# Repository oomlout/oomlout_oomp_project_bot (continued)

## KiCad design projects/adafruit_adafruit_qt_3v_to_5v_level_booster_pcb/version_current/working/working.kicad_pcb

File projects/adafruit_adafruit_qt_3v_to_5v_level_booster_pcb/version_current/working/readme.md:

# OOMP Project  
## Adafruit-QT-3V-to-5V-Level-Booster-PCB  by adafruit  
  
oomp key: oomp_projects_flat_adafruit_adafruit_qt_3v_to_5v_level_booster_pcb  
(snippet of original readme)  
  
-- Adafruit QT 3V to 5V Level Booster Breakout - STEMMA QT / Qwiic PCB  
  
<a href="http://www.adafruit.com/products/5649"><br/>  
Click here to purchase one from the Adafruit shop</a>  
  
PCB files for the Adafruit QT 3V to 5V Level Booster Breakout - STEMMA QT.   
  
Format is EagleCAD schematic and board layout  
* https://www.adafruit.com/product/5649  
  
--- Description  
  
If you're looking to use the Qwiic / Stemma QT standard for your next project - but you're using a sensor or device that requires 5V power or logic, this board is designed for you! It will let you use the 3V power and logic from your Raspberry Pi, or ARM Cortex microcontroller, and boost/shift it up to 5V for use with older or high-power devices that aren't happy with only 3V.  
  
These days, almost every microcontroller / microcomputer board has 3V power and logic: ESP32 series, ATSAMD chips, RP2040 boards, micro:bits, etc! But we still see sensors and devices here and there that really want 5V power or logic. Like this Sensirion SEN54 which has a small motor with 5V power requirements.  
  
On one side of this board is 3V power and logic level inputs. In the middle is a 5V charge-pump boosting regulator that can provide 100mA continuous (250mA peak) plus level shifting circuitry. On the opposite side is the same I2C traffic but now safely shifted up to 5V. If you happen to be using a board that wants 5V power, but 3V logic I2C, there's a solder jumper on the back you can cut/s  
  full source readme at [readme_src.md](readme_src.md)  
  
source repo at: [https://github.com/adafruit/Adafruit-QT-3V-to-5V-Level-Booster-PCB](https://github.com/adafruit/Adafruit-QT-3V-to-5V-Level-Booster-PCB)  
## Board  

## Schematic  

[schematic pdf](working_schematic.pdf)  
## Images

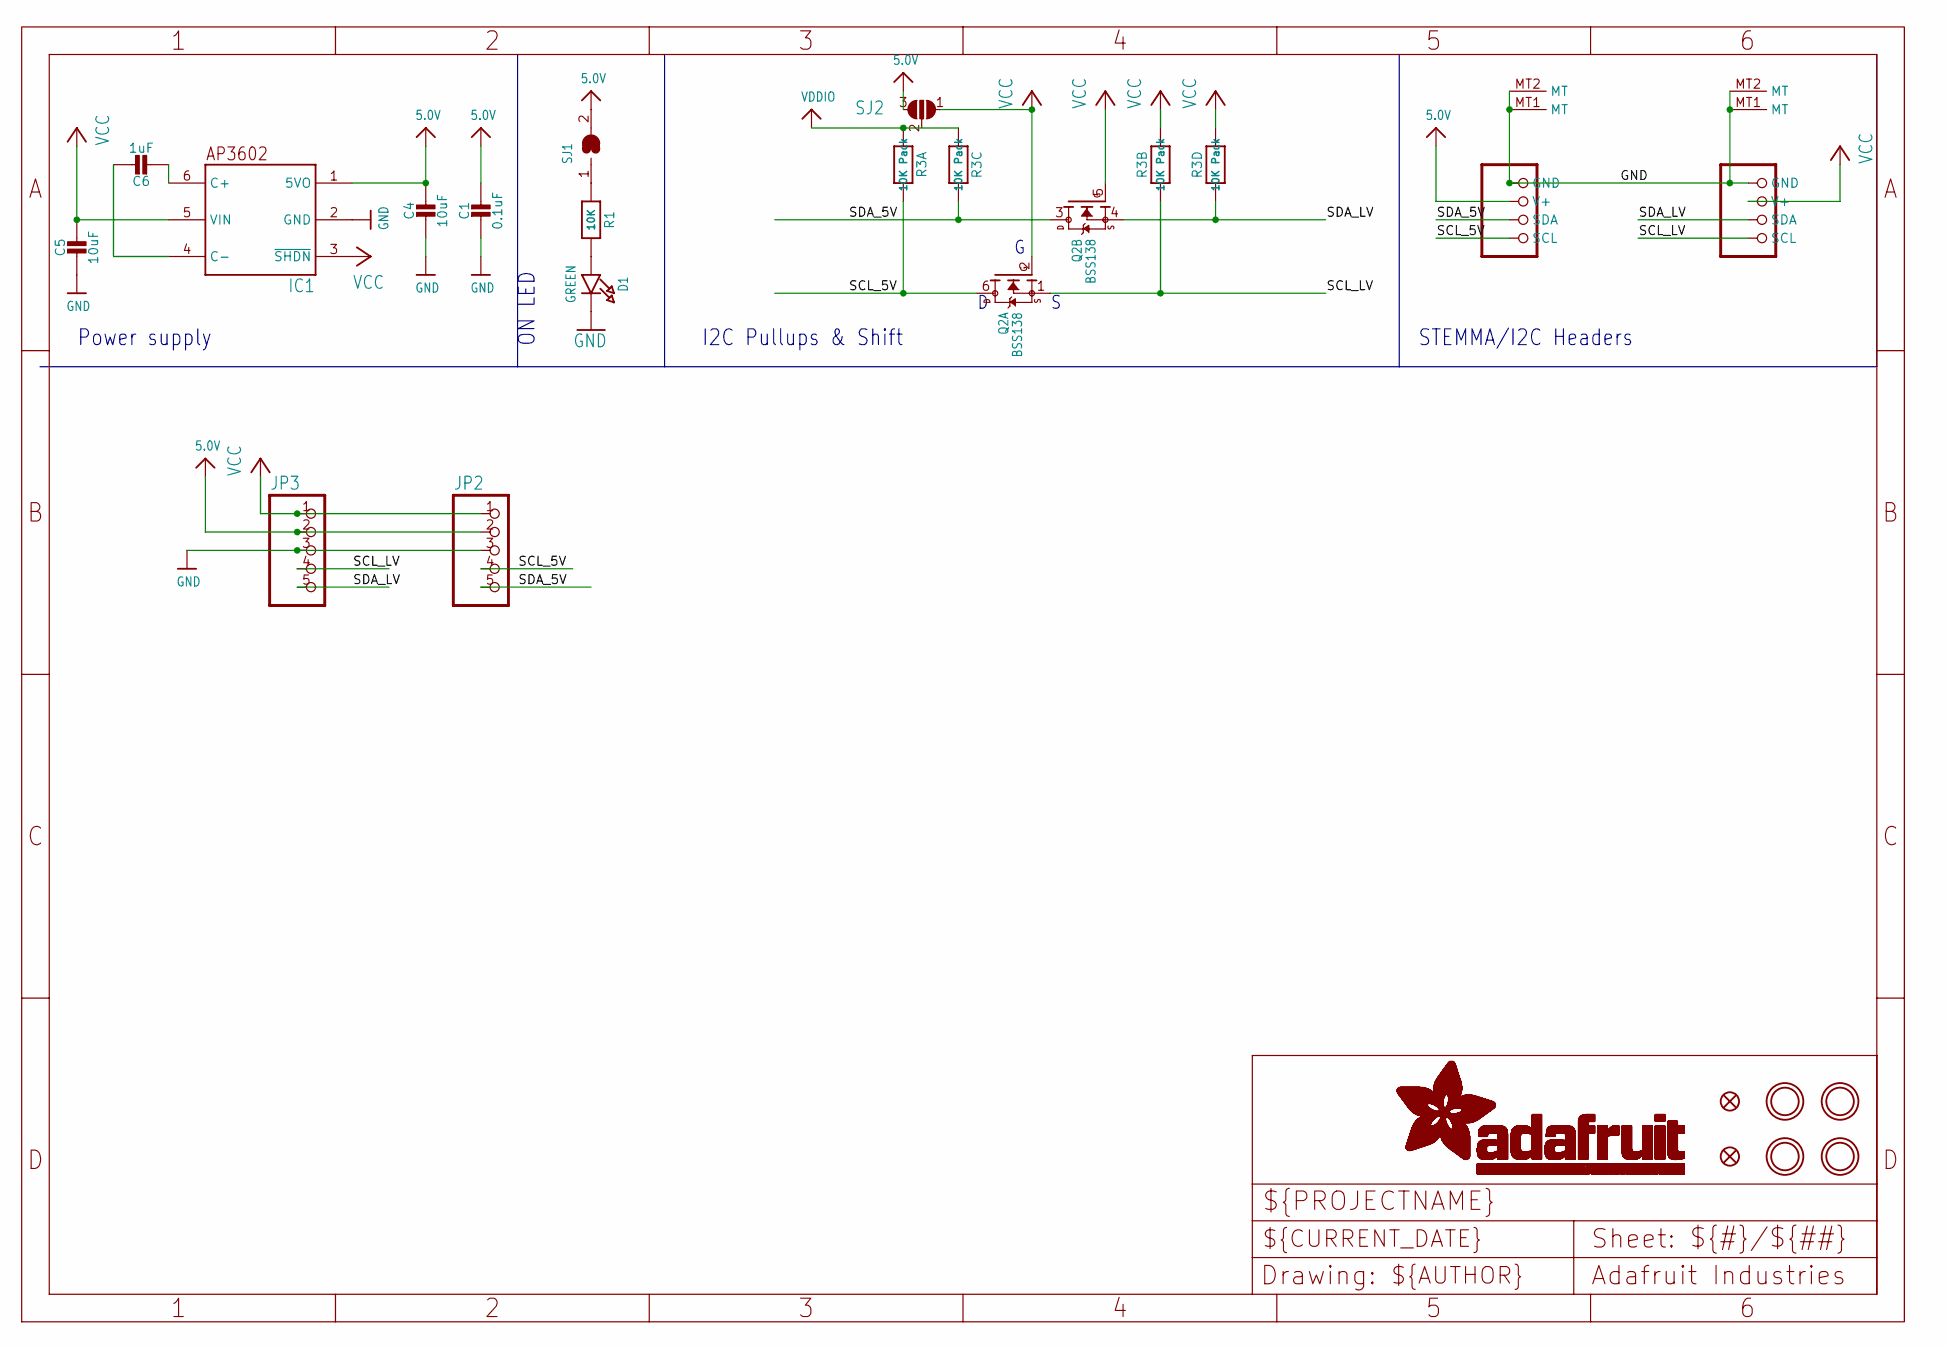
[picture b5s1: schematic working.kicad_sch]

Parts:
C1: 0.1uF; 0603-NO
C4, C5: 10uF; 0805-NO
C6: 1uF; 0805-NO
CONN3, CONN4: STEMMA_I2C_QT; JST_SH4
D1: GREEN; CHIPLED_0603_NOOUTLINE
FID3, FID4: FIDUCIAL_1MM
IC1: AP3602; SOT23-6
JP2, JP3: HEADER-1X576MIL; 1X05_ROUND_76
Q2: BSS138; SOT363
R1: 10K; 0603-NO
R3: 10K Pack; RESPACK_4X0603
SJ1: SOLDERJUMPERCLOSED; SOLDERJUMPER_CLOSEDWIRE
SJ2: SOLDERJUMPER_2WAY; SOLDERJUMPER_2WAY_OPEN_NOPASTE
U$1, U$17, U$19, U$21: MOUNTINGHOLE2.5; MOUNTINGHOLE_2.5_PLATED

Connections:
5.0V: C1.1, C4.1, CONN3.2 (V+), IC1.1 (5VO), JP2.2, JP3.2, SJ1.2, SJ2.3
GND: C1.2, C4.2, C5.2, CONN3.1 (GND), CONN3.MT1 (MT), CONN3.MT2 (MT), CONN4.1 (GND), CONN4.MT1 (MT), CONN4.MT2 (MT), D1.C, IC1.2 (GND), JP2.3, JP3.3
unnamed: D1.A, R1.2
unnamed: R1.1, SJ1.1
unnamed: C6.2, IC1.6 (C+)
unnamed: C6.1, IC1.4 (C-)
SCL_5V: CONN3.4 (SCL), JP2.4, Q2.6 (D), R3.8 (2)
SCL_LV: CONN4.4 (SCL), JP3.4, Q2.1 (S), R3.7 (2)
SDA_5V: CONN3.3 (SDA), JP2.5, Q2.3 (D), R3.6 (2)
SDA_LV: CONN4.3 (SDA), JP3.5, Q2.4 (S), R3.5 (2)
VCC: C5.1, CONN4.2 (V+), IC1.3 (~SHDN), IC1.5 (VIN), JP2.1, JP3.1, Q2.2 (G), Q2.5 (G), R3.2 (1), R3.4 (1), SJ2.1
VDDIO: R3.1, R3.3 (1), SJ2.2

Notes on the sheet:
ON LED
Power supply
STEMMA/I2C Headers
I2C Pullups & Shift

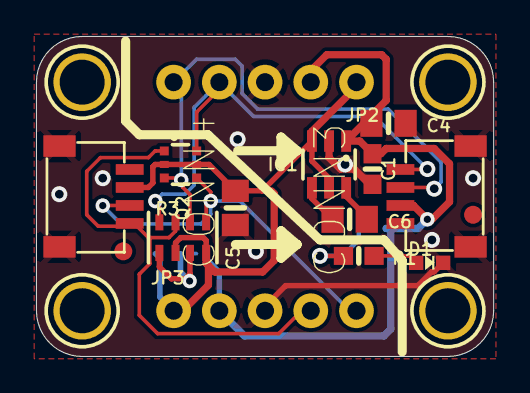
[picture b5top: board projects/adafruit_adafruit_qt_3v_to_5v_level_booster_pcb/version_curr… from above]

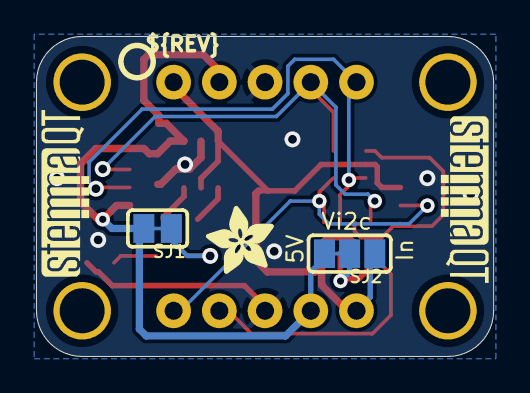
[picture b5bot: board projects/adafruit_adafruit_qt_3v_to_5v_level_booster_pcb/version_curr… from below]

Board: 2 copper layers, 25.4 x 17.8 mm, 40 parts (8 on the bottom side), 12 nets.

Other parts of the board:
PLABEL0: PLABEL0
PLABEL1: PLABEL1
PLABEL2: PLABEL2
PLABEL3: PLABEL3
PLABEL4: PLABEL4
PLABEL5: PLABEL5
PLABEL6: PLABEL6
PLABEL7: PLABEL7
PLABEL8: PLABEL8
PLABEL9: PLABEL9
PLABEL10: PLABEL10
PLABEL11: PLABEL11
PLABEL12: PLABEL12
PLABEL13: PLABEL13
PLABEL14: PLABEL14
U$2: ADAFRUIT_3.5MM
U$25: PCBFEAT-REV-040
U$30, U$31: STEMMAQT

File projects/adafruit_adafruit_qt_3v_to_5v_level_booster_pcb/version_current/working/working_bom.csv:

Row,Description,Part,References,Value,Footprint,Quantity Per PCB,Status,Datasheet
1,,CAP_CERAMIC0603_NO,C1,0.1uF,0603-NO,1, ,
2,,CAP_CERAMIC0805-NOOUTLINE,C6,1uF,0805-NO,1, ,
3,,CAP_CERAMIC0805-NOOUTLINE,C4 C5,10uF,0805-NO,2, ,
4,,STEMMA_I2C_QT,CONN3 CONN4,STEMMA_I2C_QT,JST_SH4,2, ,
5,,LED0603_NOOUTLINE,D1,GREEN,CHIPLED_0603_NOOUTLINE,1, ,
6,,AP3602,IC1,AP3602,SOT23-6,1, ,
7,,HEADER-1X576MIL,JP2 JP3,HEADER-1X576MIL,1X05_ROUND_76,2, ,
8,,MOSFET-N_DUAL,Q2,BSS138,SOT363,1, ,
9,,RESISTOR_0603_NOOUT,R1,10K,0603-NO,1, ,
10,,RESISTOR_4PACK,R3,10K Pack,RESPACK_4X0603,1, ,





Project info:
Schematic:,working
Variant:,default
Revision:,
Date:,2023-08-03_17-21-23
KiCad Version:,7.0.6-7.0.6~ubuntu22.04.1
Statistics:
Component Groups:,10
Component Count:,13 (0 SMD/ 0 THT)
Fitted Components:,13 (0 SMD/ 0 THT)
Number of PCBs:,1
Total Components:,13

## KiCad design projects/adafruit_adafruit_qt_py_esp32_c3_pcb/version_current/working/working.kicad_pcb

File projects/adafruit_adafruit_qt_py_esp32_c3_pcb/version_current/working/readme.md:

# OOMP Project  
## Adafruit-QT-Py-ESP32-C3-PCB  by adafruit  
  
oomp key: oomp_projects_flat_adafruit_adafruit_qt_py_esp32_c3_pcb  
(snippet of original readme)  
  
-- Adafruit QT Py ESP32-C3 WiFi Dev Board with STEMMA QT PCB  
  
<a href="http://www.adafruit.com/products/5405"><br/>  
Click here to purchase one from the Adafruit shop</a>  
  
PCB files for the Adafruit QT Py ESP32-C3 WiFi Dev Board with STEMMA QT.   
  
Format is EagleCAD schematic and board layout  
* https://www.adafruit.com/product/5405  
  
--- Description  
  
What's life without a little RISC? This miniature dev board is perfect for small projects: it comes with our favorite connector - the STEMMA QT, a chainable I2C port, WiFi, Bluetooth LE, and plenty of FLASH and RAM memory for many IoT projects. What a cutie pie! Or is it... a QT Py? This diminutive dev board comes with a RISC-V IoT microcontroller, the ESP32-C3!  
  
ESP32-C3 is a low-cost microcontroller from Espressif that supports 2.4 GHz Wi-Fi and Bluetooth® Low Energy (Bluetooth LE). It has built-in USB-to-Serial, but not native USB - it cannot act as a keyboard or disk drive. The chip used here has 4MB of Flash memory, 400 KB of SRAM and can easily handle TLS connections.  
  
The ESP32-C3 integrates a rich set of peripherals, ranging from UART, I2C, I2S, remote control peripheral, LED PWM controller, general DMA controller, TWAI controller, USB Serial/JTAG controller, temperature sensor, and ADC. It also includes SPI, Dual SPI, and Quad SPI interfaces. There is no DAC or native capacitive touch.  
  
There's a minimum number of pins on this chip, it's specifically designed to be low cost   
  full source readme at [readme_src.md](readme_src.md)  
  
source repo at: [https://github.com/adafruit/Adafruit-QT-Py-ESP32-C3-PCB](https://github.com/adafruit/Adafruit-QT-Py-ESP32-C3-PCB)  
## Board  

## Schematic  

[schematic pdf](working_schematic.pdf)  
## Images

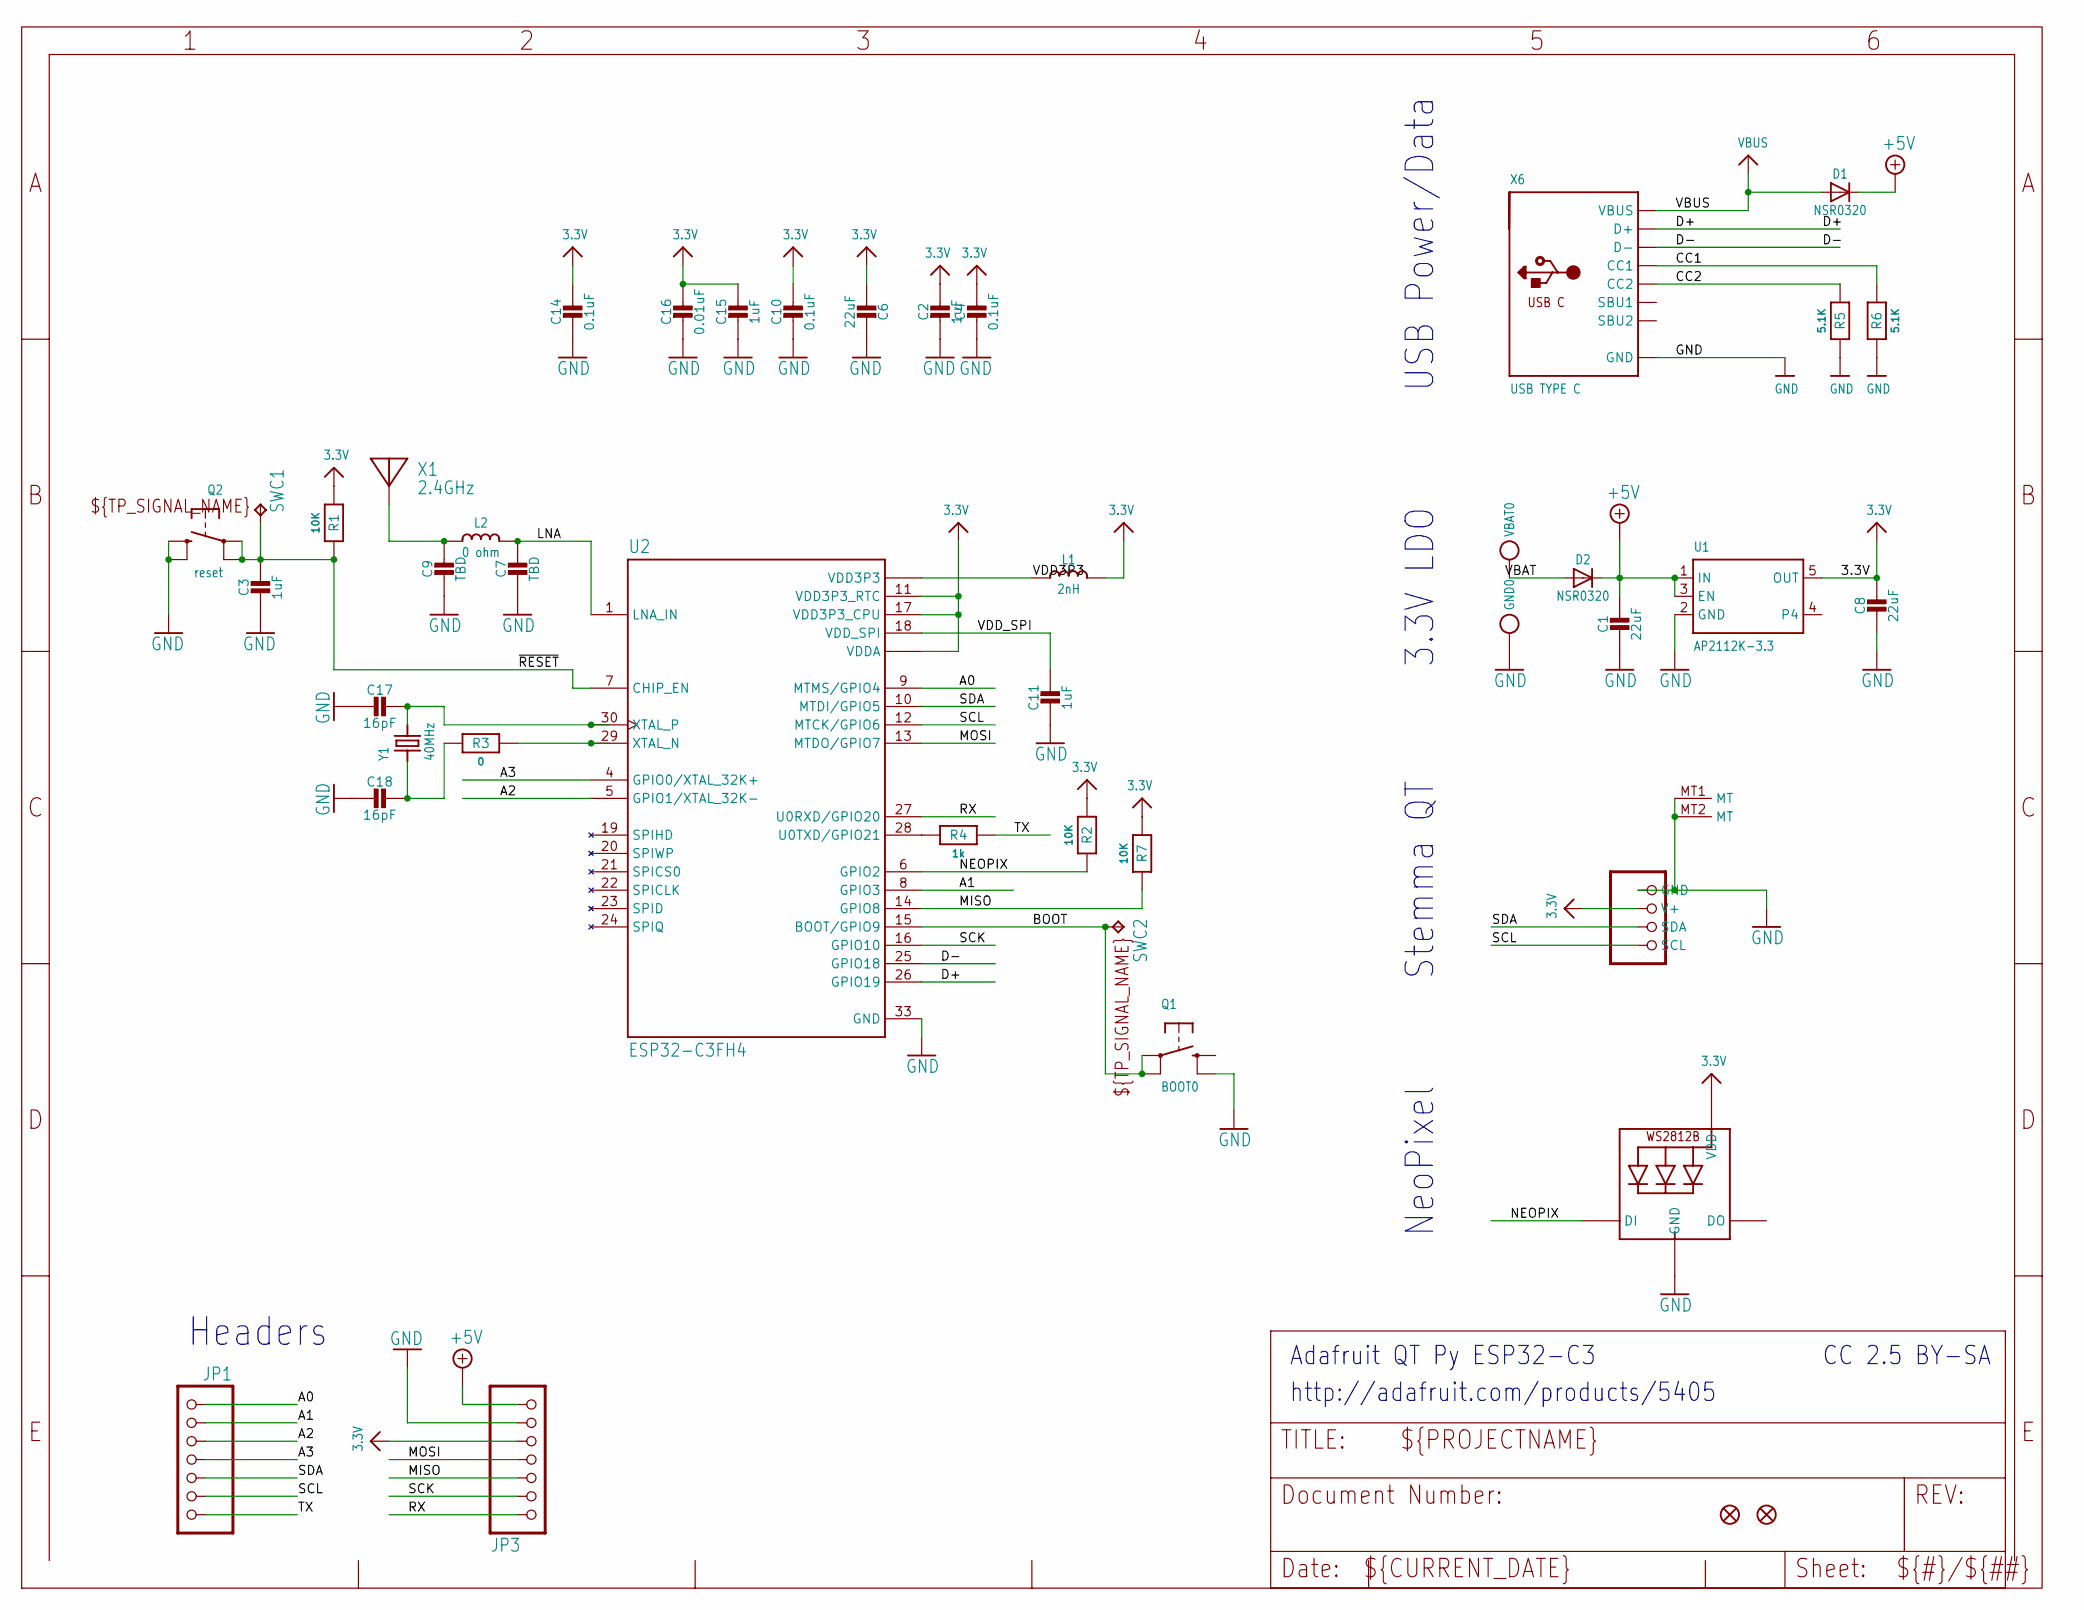
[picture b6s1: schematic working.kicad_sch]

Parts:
C1, C6, C8: 22uF; 0805-NO
C2, C3, C11, C15: 1uF; _0402NO
C4, C10, C14: 0.1uF; _0402NO
C7, C9: TBD; _0402NO
C16: 0.01uF; _0402NO
C17, C18: 16pF; _0402NO
CONN1: STEMMA_I2C_QTSKINNY; JST_SH4_SKINNY
D1, D2: NSR0320; SOD-323_MINI
GND0: TESTPOINT_MINUS; TESTPOINT_MINUS_1X3MM
JP1, JP3: HEADER-1X7_CASTEL; 1X07_CASTEL
L1: 2nH; _0402
L2: 0 ohm; _0402
LED1: WS2812B_SK6805_1515; SK6805_1515
Q1: BOOT0; BTN_KMR2_4.6X2.8
Q2: reset; BTN_KMR2_SLIM
R1, R2: 10K; _0402NO
R3: 0; _0402NO
R4: 1k; _0402NO
R5, R6: 5.1K; _0402NO
R7: 10K; _0603MP_TWO6MIL
SWC1, SWC2: TPB1,27; B1,27
U1: AP2112K-3.3; SOT23-5
U2: ESP32-C3FH4; QFN32_5MM
U$6, U$8: FIDUCIAL_1MM
VBAT0: TESTPOINT_PLUS13; TESTPOINT_PLUS_1X3MM
X1: 2.4GHz; ANT_2450AT18B100
X6: USB TYPE C; USB_C_CUSB31-CFM2AX-01-X
Y1: 40MHz; CRYSTAL_2X1.6

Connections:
3.3V: C2.1, C4.1, C6.1, C8.1, C10.1, C14.1, C15.1, C16.1, CONN1.2 (V+), JP3.5, JP3.5C (5), L1.1, LED1.2 (VDD), R1.1, R2.1, R7.1, U1.5 (OUT), U2.11 (VDD3P3_RTC), U2.17 (VDD3P3_CPU), U2.31 (VDDA), U2.32 (VDDA)
+5V: C1.1, D1.C, D2.C, JP3.7, JP3.7C (7), U1.1 (IN), U1.3 (EN)
A0: JP1.1, JP1.1C (1), U2.9 (MTMS/GPIO4)
A1: JP1.2, JP1.2C (2), U2.8 (GPIO3)
A2: JP1.3, JP1.3C (3), U2.5 (GPIO1/XTAL_32K-)
A3: JP1.4, JP1.4C (4), U2.4 (GPIO0/XTAL_32K+)
BOOT: Q1.A, Q1.A' (P1), SWC2.TP, U2.15 (BOOT/GPIO9)
CC1: R6.2, X6.A5 (CC1)
CC2: R5.2, X6.B5 (CC2)
D+: U2.26 (GPIO19), X6.A6 (D+), X6.B6 (D+)
D-: U2.25 (GPIO18), X6.A7 (D-), X6.B7 (D-)
GND: C1.2, C2.2, C3.2, C4.2, C6.2, C7.2, C8.2, C9.2, C10.2, C11.2, C14.2, C15.2, C16.2, C17.2, C18.2, CONN1.1 (GND), CONN1.MT1 (MT), CONN1.MT2 (MT), GND0.P$1, JP3.6, JP3.6C (6), LED1.4 (GND), Q1.B' (S1), Q2.B (S), Q2.B' (S1), R5.1, R6.1, U1.2 (GND), U2.33 (GND), X6.A1B12 (GND), X6.B1A12 (GND)
LNA: C7.1, L2.2, U2.1 (LNA_IN)
MISO: JP3.3, JP3.3C (3), R7.2, U2.14 (GPIO8)
MOSI: JP3.4, JP3.4C (4), U2.13 (MTDO/GPIO7)
unnamed: R4.1, U2.28 (U0TXD/GPIO21)
unnamed: C9.1, L2.1, X1.FP
unnamed: R3.2, U2.29 (XTAL_N)
unnamed: C17.1, U2.30 (XTAL_P), Y1.3 (2)
unnamed: C18.1, R3.1, Y1.1
NEOPIX: LED1.1 (DI), R2.2, U2.6 (GPIO2)
RX: JP3.1, JP3.1C (1), U2.27 (U0RXD/GPIO20)
SCK: JP3.2, JP3.2C (2), U2.16 (GPIO10)
SCL: CONN1.4 (SCL), JP1.6, JP1.6C (6), U2.12 (MTCK/GPIO6)
SDA: CONN1.3 (SDA), JP1.5, JP1.5C (5), U2.10 (MTDI/GPIO5)
TX: JP1.7, JP1.7C (7), R4.2
VBAT: D2.A, VBAT0.P$1
VBUS: D1.A, X6.A4B9 (VBUS), X6.B4A9 (VBUS)
VDD3P3: L1.2, U2.2 (VDD3P3), U2.3 (VDD3P3)
VDD_SPI: C11.1, U2.18 (VDD_SPI)
~RESET: C3.1, Q2.A, Q2.A' (P1), R1.2, SWC1.TP, U2.7 (CHIP_EN)

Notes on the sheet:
NeoPixel
http://adafruit.com/products/5405
Stemma QT
USB Power/Data
Adafruit QT Py ESP32-C3
3.3V LDO
CC 2.5 BY-SA
Headers

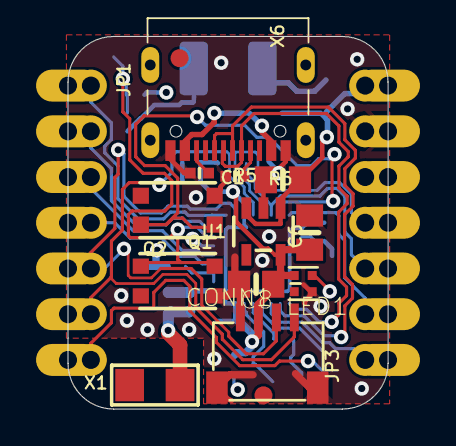
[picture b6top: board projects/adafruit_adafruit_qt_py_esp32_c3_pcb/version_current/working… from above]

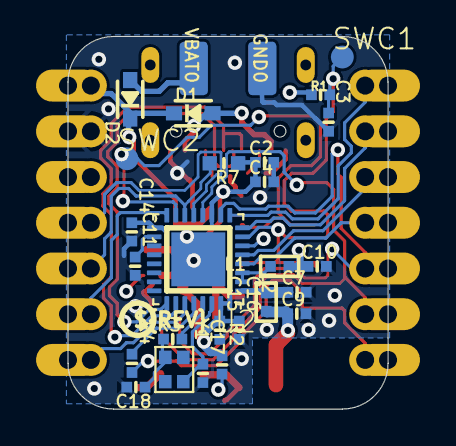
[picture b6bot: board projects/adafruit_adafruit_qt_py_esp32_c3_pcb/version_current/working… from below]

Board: 4 copper layers, 17.8 x 20.7 mm, 46 parts (29 on the bottom side), 31 nets.

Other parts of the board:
U$3: QTPYC3_TOP
U$12: PCBFEAT-REV-040
U$18: QTPYC3_BOT

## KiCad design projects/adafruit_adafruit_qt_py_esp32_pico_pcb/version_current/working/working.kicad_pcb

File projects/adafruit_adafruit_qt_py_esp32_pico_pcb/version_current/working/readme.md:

# OOMP Project  
## Adafruit-QT-Py-ESP32-Pico-PCB  by adafruit  
  
oomp key: oomp_projects_flat_adafruit_adafruit_qt_py_esp32_pico_pcb  
(snippet of original readme)  
  
-- Adafruit QT Py ESP32 Pico - WiFi Dev Board with STEMMA QT  
  
<a href="http://www.adafruit.com/products/5395"><br/>  
Click here to purchase one from the Adafruit shop</a>  
  
PCB files for the Adafruit QT Py ESP32 Pico.  
  
Format is EagleCAD schematic and board layout  
* https://www.adafruit.com/product/5395  
  
--- Description  
  
This dev board is like when you're watching a super-hero movie and the protagonist shows up in a totally amazing costume in the third act and you're like 'OMG! That's the hero and they're here to kick some serious butt!" but in this case its a microcontroller.  
  
This QT Py board is a thumbnail-sized PCB that features the ESP32 Pico V3 02, an all-in-one chip that has an ESP32 chip with dual-core 240MHz Tensilica processor, WiFi and Bluetooth classic + BLE, adds a bunch of required passives and oscillator, 8 MB of Flash memory and 2 MB of PSRAM. We add a USB to serial converter chip, some more passives, an antenna, USB C, buttons, NeoPixel and QT connector to outfit this super-hero chip for any task you want to throw it at.  
  
At the core of ESP32-PICO-V3-02 is the ESP32 (ECO V3) chip, which is a single 2.4 GHz Wi-Fi and Bluetooth combo chip designed with TSMC’s 40 nm low-power technology. ESP32-PICO-V3-02 integrates all peripheral components seamlessly, including a crystal oscillator, flash, PSRAM, filter capacitors, and RF matching links in one single package. This makes it perfect for stuffing into such a small sp  
  full source readme at [readme_src.md](readme_src.md)  
  
source repo at: [https://github.com/adafruit/Adafruit-QT-Py-ESP32-Pico-PCB](https://github.com/adafruit/Adafruit-QT-Py-ESP32-Pico-PCB)  
## Board  

## Schematic  

[schematic pdf](working_schematic.pdf)  
## Images

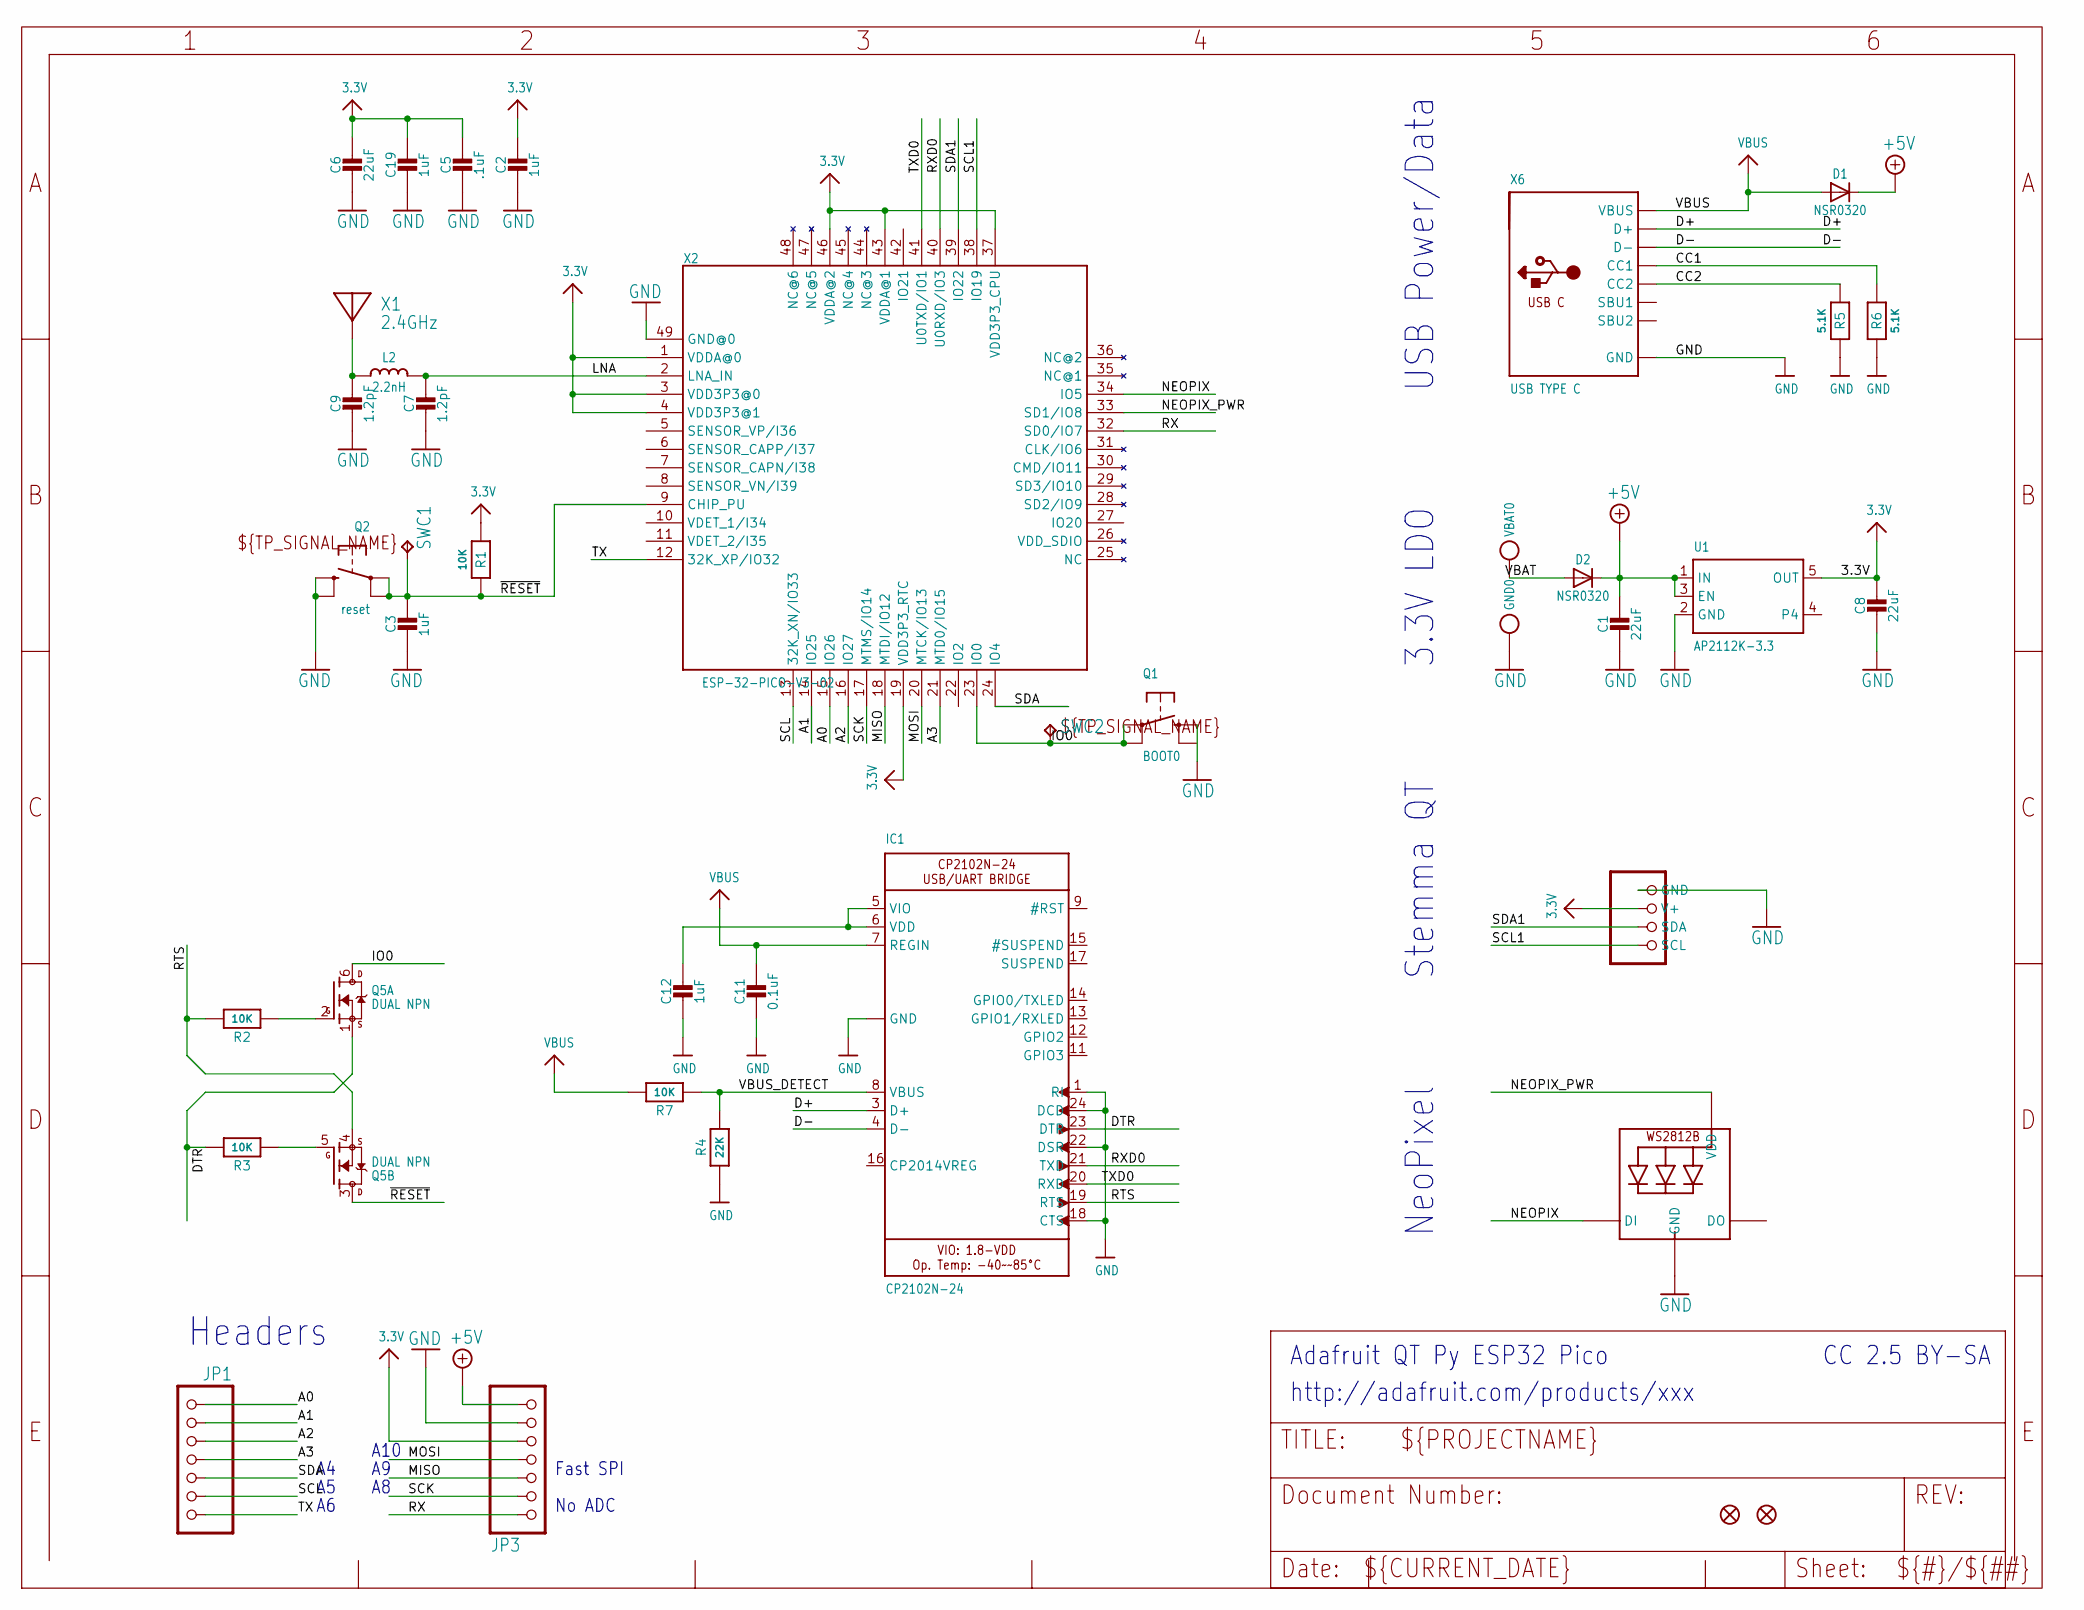
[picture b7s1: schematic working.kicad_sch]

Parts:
C1, C6, C8: 22uF; 0805-NO
C2, C3, C12: 1uF; _0402NO
C5: .1uF; _0402NO
C7, C9: 1.2pF; _0402NO
C11: 0.1uF; _0402NO
C19: 1uF; 0603-NO_WIDE
CONN1: STEMMA_I2C_QTSKINNY; JST_SH4_SKINNY
D1, D2: NSR0320; SOD-323_MINI
GND0: TESTPOINT_MINUS; TESTPOINT_MINUS_1X3MM
IC1: CP2102N-24; QFN24_4MM_SMSC
JP1, JP3: HEADER-1X7_CASTEL; 1X07_CASTEL
L2: 2.2nH; _0402
LED1: WS2812B_SK6805_1515; SK6805_1515
Q1: BOOT0; BTN_KMR2_4.6X2.8
Q2: reset; BTN_KMR2_4.6X2.8
Q5: DUAL NPN; SOT363
R1, R2, R3, R7: 10K; _0402NO
R4: 22K; _0402NO
R5, R6: 5.1K; _0402NO
SWC1, SWC2: TPB1,27; B1,27
U1: AP2112K-3.3; SOT23-5
U$6, U$8: FIDUCIAL_1MM
VBAT0: TESTPOINT_PLUS13; TESTPOINT_PLUS_1X3MM
X1: 2.4GHz; ANT_2450AT18B100
X2: ESP-32-PICO-V3-02; QFN48_7X7
X6: USB TYPE C; USB_C_CUSB31-CFM2AX-01-X

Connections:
3.3V: C2.1, C5.1, C6.1, C8.1, C19.1, CONN1.2 (V+), JP3.5, JP3.5C (5), R1.1, U1.5 (OUT), X2.1 (VDDA@0), X2.3 (VDD3P3@0), X2.4 (VDD3P3@1), X2.19 (VDD3P3_RTC), X2.37 (VDD3P3_CPU), X2.43 (VDDA@1), X2.46 (VDDA@2)
+5V: C1.1, D1.C, D2.C, JP3.7, JP3.7C (7), U1.1 (IN), U1.3 (EN)
A0: JP1.1, JP1.1C (1), X2.15 (IO26)
A1: JP1.2, JP1.2C (2), X2.14 (IO25)
A2: JP1.3, JP1.3C (3), X2.16 (IO27)
A3: JP1.4, JP1.4C (4), X2.21 (MTD0/IO15)
CC1: R6.2, X6.A5 (CC1)
CC2: R5.2, X6.B5 (CC2)
D+: IC1.3 (D+), X6.A6 (D+), X6.B6 (D+)
D-: IC1.4 (D-), X6.A7 (D-), X6.B7 (D-)
DTR: IC1.23 (DTR), Q5.1 (S), R3.2
GND: C1.2, C2.2, C3.2, C5.2, C6.2, C7.2, C8.2, C9.2, C11.2, C12.2, C19.2, CONN1.1 (GND), GND0.P$1, IC1.1 (RI), IC1.2 (GND), IC1.18 (CTS), IC1.22 (DSR), IC1.24 (DCD), IC1.THERM (GND), JP3.6, JP3.6C (6), LED1.4 (GND), Q1.B (S), Q1.B' (S1), Q2.B (S), Q2.B' (S1), R4.1, R5.1, R6.1, U1.2 (GND), X2.49 (GND@0), X6.A1B12 (GND), X6.B1A12 (GND)
IO0: Q1.A, Q1.A' (P1), Q5.6 (D), SWC2.TP, X2.23 (IO0)
LNA: C7.1, L2.2, X2.2 (LNA_IN)
MISO: JP3.3, JP3.3C (3), X2.18 (MTDI/IO12)
MOSI: JP3.4, JP3.4C (4), X2.20 (MTCK/IO13)
unnamed: C12.1, IC1.5 (VIO), IC1.6 (VDD)
unnamed: C9.1, L2.1, X1.FP
unnamed: Q5.5 (G), R3.1
unnamed: Q5.2 (G), R2.1
NEOPIX: LED1.1 (DI), X2.34 (IO5)
NEOPIX_PWR: LED1.2 (VDD), X2.33 (SD1/IO8)
RTS: IC1.19 (RTS), Q5.4 (S), R2.2
RX: JP3.1, JP3.1C (1), X2.32 (SD0/IO7)
RXD0: IC1.21 (TXD), X2.40 (U0RXD/IO3)
SCK: JP3.2, JP3.2C (2), X2.17 (MTMS/IO14)
SCL: JP1.6, JP1.6C (6), X2.13 (32K_XN/IO33)
SCL1: CONN1.4 (SCL), X2.38 (IO19)
SDA: JP1.5, JP1.5C (5), X2.24 (IO4)
SDA1: CONN1.3 (SDA), X2.39 (IO22)
TX: JP1.7, JP1.7C (7), X2.12 (32K_XP/IO32)
TXD0: IC1.20 (RXD), X2.41 (U0TXD/IO1)
VBAT: D2.A, VBAT0.P$1
VBUS: C11.1, D1.A, IC1.7 (REGIN), R7.2, X6.A4B9 (VBUS), X6.B4A9 (VBUS)
VBUS_DETECT: IC1.8 (VBUS), R4.2, R7.1
~RESET: C3.1, Q2.A, Q2.A' (P1), Q5.3 (D), R1.2, SWC1.TP, X2.9 (CHIP_PU)

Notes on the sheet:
USB Power/Data
Fast SPI
A10
No ADC
Adafruit QT Py ESP32 Pico
Headers
3.3V LDO
CC 2.5 BY-SA
NeoPixel
http://adafruit.com/products/xxx
Stemma QT

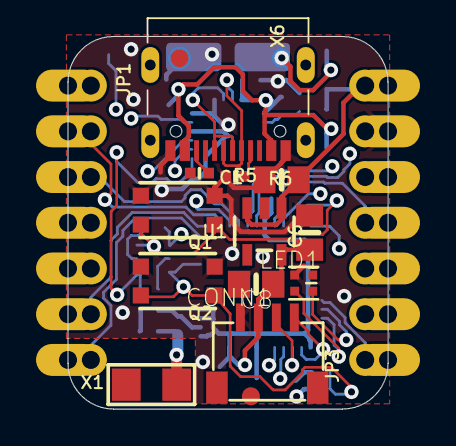
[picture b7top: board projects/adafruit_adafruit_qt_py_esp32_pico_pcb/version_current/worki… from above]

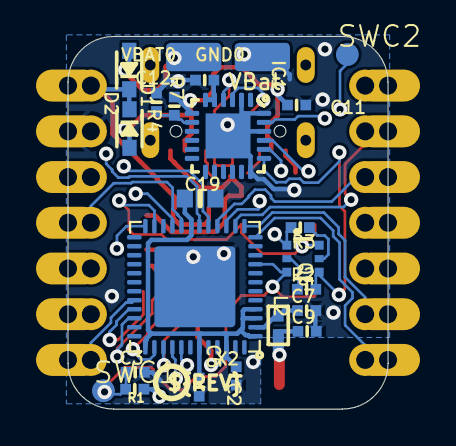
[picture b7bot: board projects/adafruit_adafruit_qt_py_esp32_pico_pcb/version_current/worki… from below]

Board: 4 copper layers, 17.8 x 20.7 mm, 42 parts (25 on the bottom side), 36 nets.

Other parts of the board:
U$3: QTPY_ESP32_BOT
U$12: PCBFEAT-REV-040
U$22: QTPY_ESP32_TOP
